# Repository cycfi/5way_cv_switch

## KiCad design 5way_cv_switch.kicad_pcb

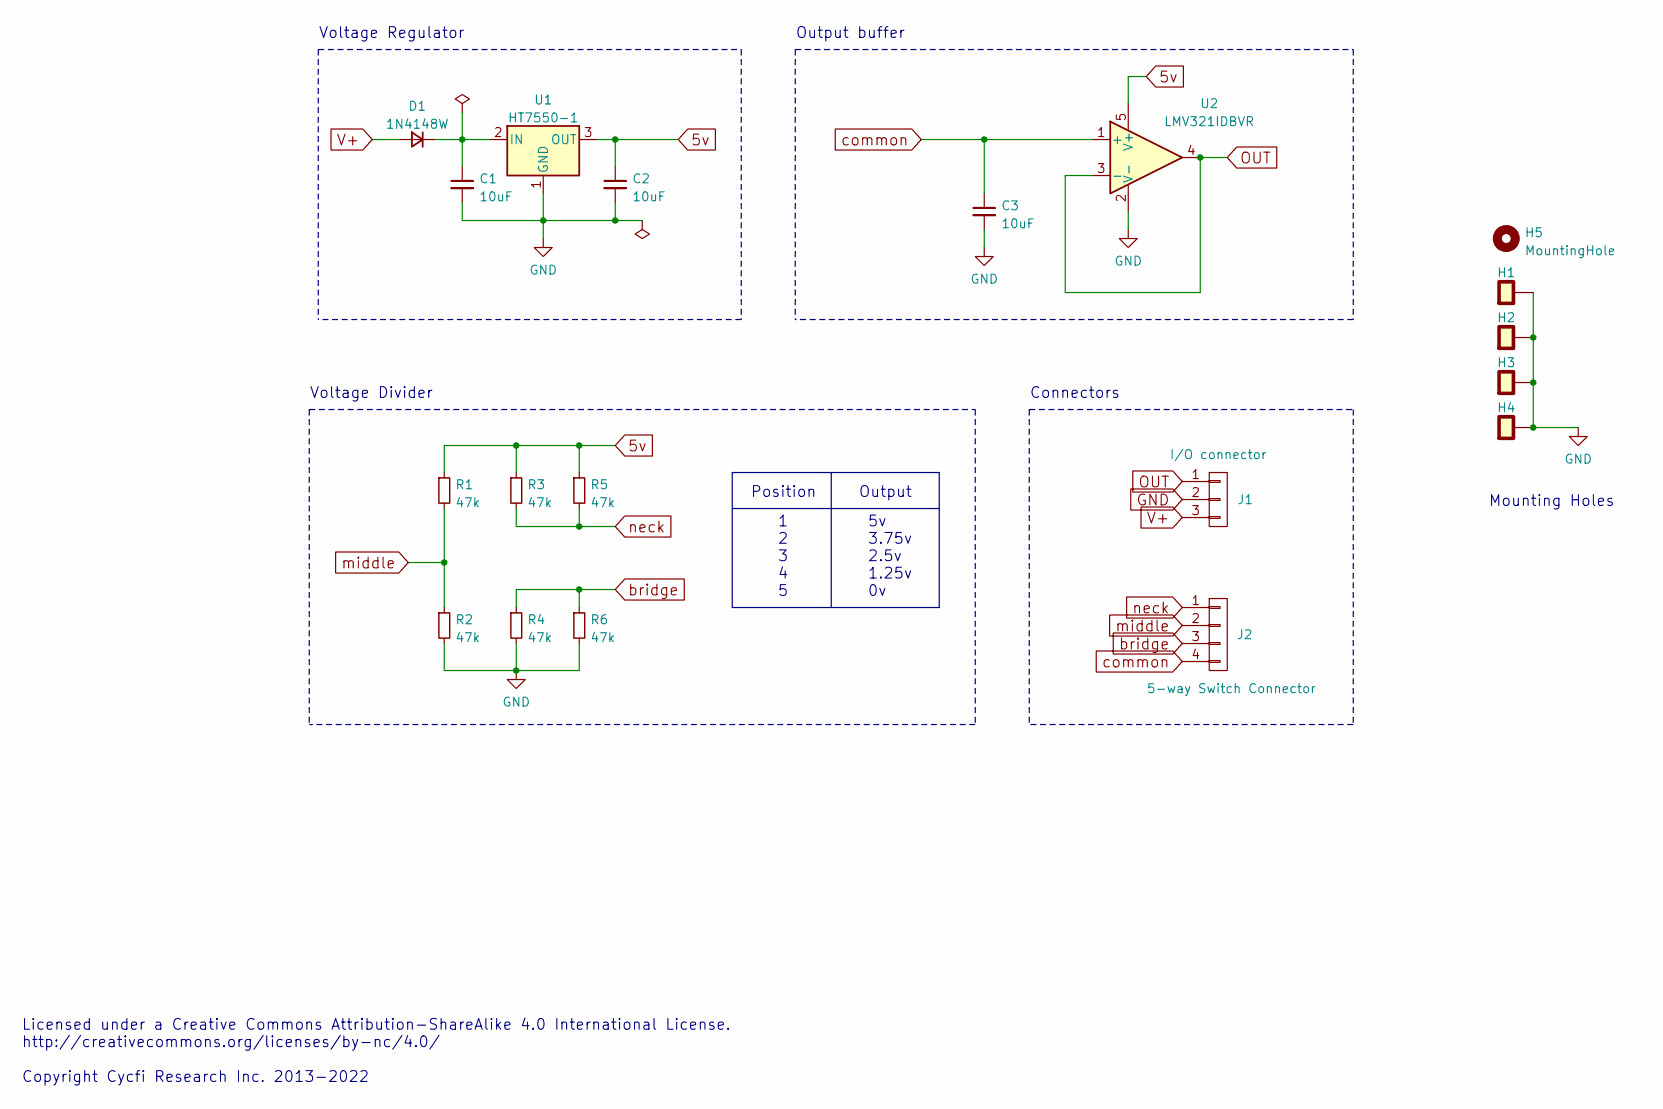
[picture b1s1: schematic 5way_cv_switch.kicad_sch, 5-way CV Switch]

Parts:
C1, C2, C3: 10uF; C_0805_2012Metric; LCSC C15850
D1: 1N4148W; D_SOD-123; LCSC C81598
H1, H2, H3, H4: single_pad; cond_hole_rect_1.2x3.5mm
H5: MountingHole; hole_2.65mm
J1: I/O connector; pin_header_1x3p_2.54mm_smd_horizontal
J2: 5-way Switch Connector; 5way_switch
R1, R2, R3, R4, R5, R6: 47k; R_0402_1005Metric; LCSC C25792
U1: HT7550-1; SOT-89-3; LCSC C16106
U2: LMV321IDBVR; SOT-23-5; LCSC C7972

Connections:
5v: C2.1, R1.1, R3.1, R5.1, U1.3 (OUT), U2.5 (V+)
GND: C1.2, C2.2, C3.2, H1.1, H2.1, H3.1, H4.1, J1.2, R2.2, R4.2, R6.2, U1.1 (GND), U2.2 (V-)
unnamed: C1.1, D1.1 (K), U1.2 (IN)
OUT: J1.1, U2.3 (-), U2.4
V+: D1.2 (A), J1.3
bridge: J2.3, R4.1, R6.1
common: C3.1, J2.4, U2.1 (+)
middle: J2.2, R1.2, R2.1
neck: J2.1, R3.2, R5.2

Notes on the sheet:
Output
5v 3.75v 2.5v 1.25v 0v
Connectors
Voltage Divider
1 2 3 4 5
Licensed under a Creative Commons Attribution-ShareAlike 4.0 International License. http://creativecommons.org/licenses/by-nc/4.0/ Copyright Cycfi Research Inc. 2013-2022
Output buffer
Voltage Regulator
Position
Mounting Holes

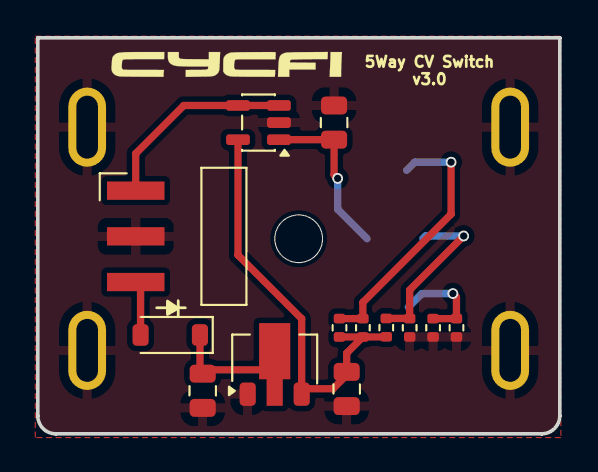
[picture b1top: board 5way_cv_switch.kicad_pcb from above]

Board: 2 copper layers, 29.0 x 22.0 mm, 19 parts (1 on the bottom side), 9 nets.

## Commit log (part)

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2022-03-01 Added dedicated 5-way CV switch
2022-03-01 minor updates
2022-03-01 Added small CV Pot
2022-04-16 Updated components for JLCPCB PCBA
2022-04-18 PCB fabrication
2022-06-07 Added diode markings in the silkscreen
2022-06-09 Updates: - Fixed overlapping fill regions when paneling - Added JLCPCB rotation
2023-01-22 Added fab and updates
